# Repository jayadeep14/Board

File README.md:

# Custom Esp32 Board

This project is a custom-designed breakout board for the ESP32-S3 chip, created using KiCad 9. 
The board features native USB-C programming support, and includes an integrated Li-Ion battery charger, gyroscope 

# Hardware
Features
-ESP32-S3 Microcontroller

-USB-C Port

Used for both power input and firmware flashing

-Li-Ion Battery Charging Circuit

Integrated charger IC with status indicators

Supports single-cell Li-Ion/LiPo batteries
gyroscope 
-Compact Breakout Form Factor

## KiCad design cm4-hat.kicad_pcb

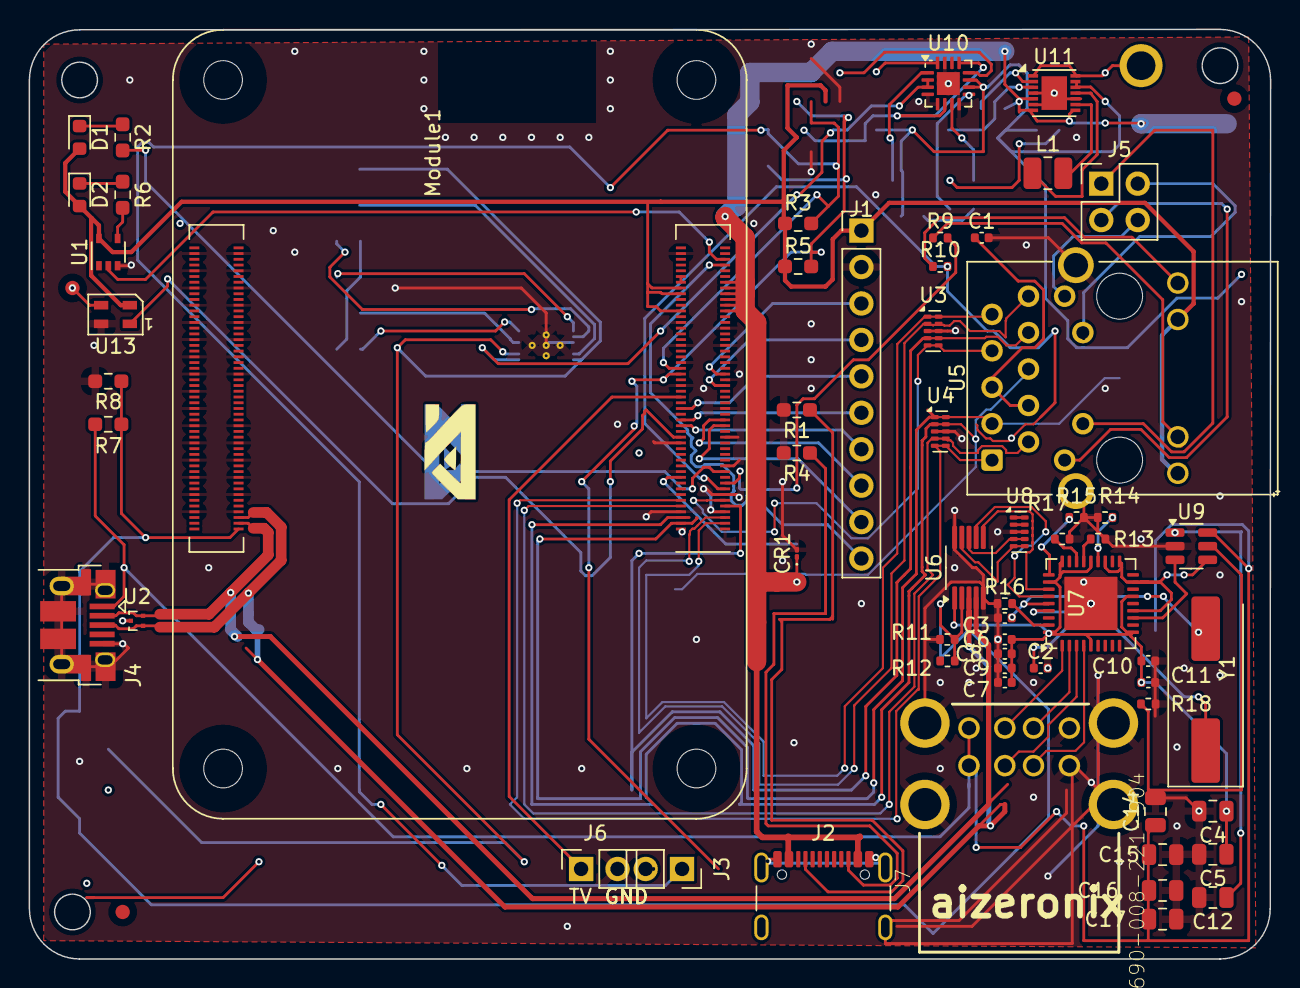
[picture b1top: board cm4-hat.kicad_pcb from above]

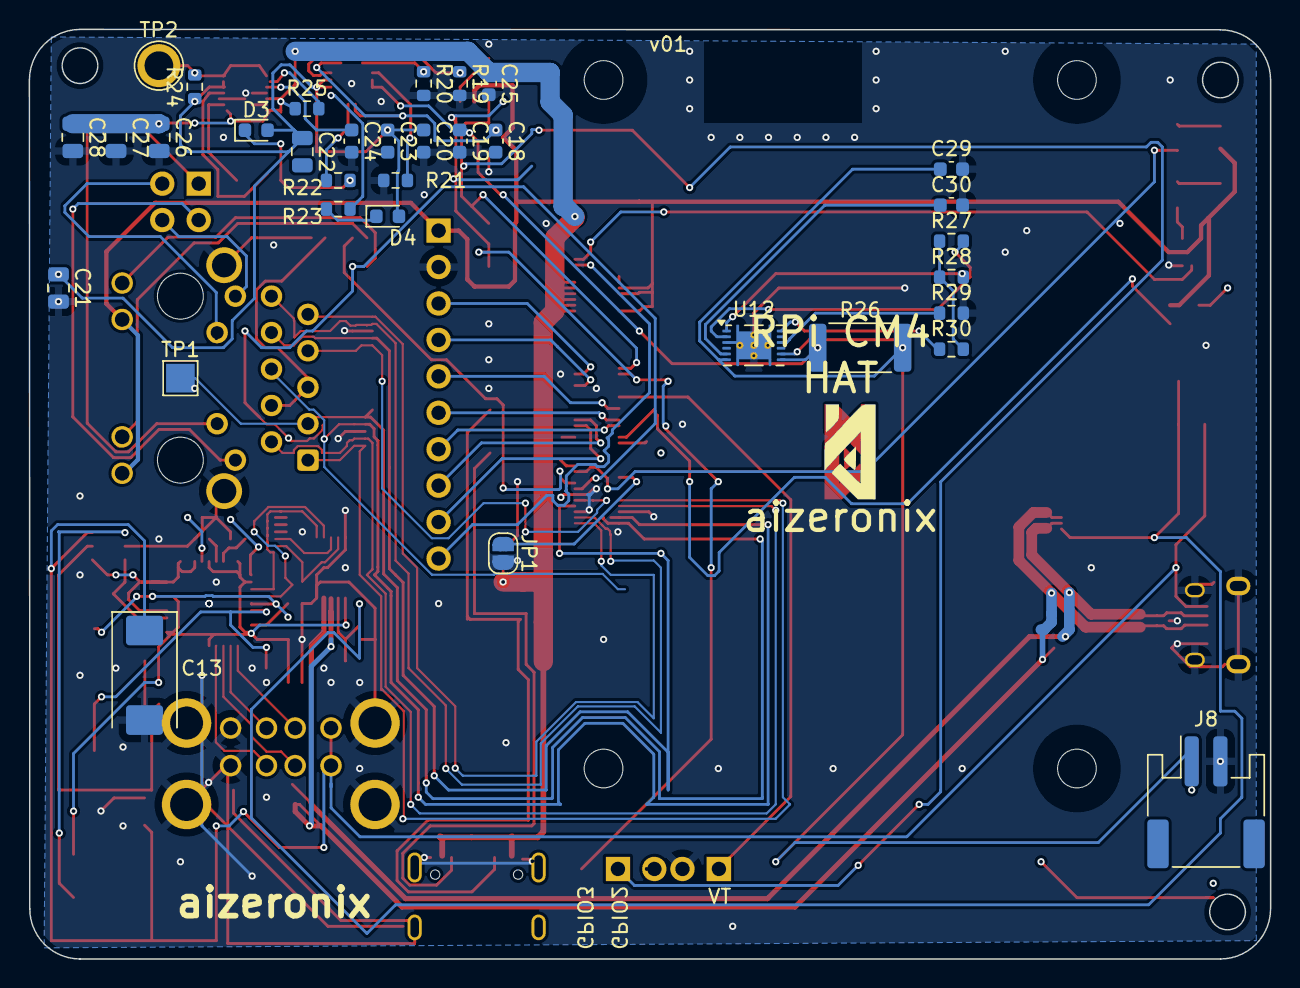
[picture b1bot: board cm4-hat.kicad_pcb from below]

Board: 2 copper layers, 86.5 x 64.8 mm, 94 parts (34 on the bottom side), 90 nets.

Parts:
C1, C6, C7, C8, C9, C10, C11: 100n; C_0402_1005Metric
C2, C3: 27pF; C_0402_1005Metric
C4, C5, C12, C14, C15, C16, C17: 10u; C_0805_2012Metric
C13: 100uF; CP_EIA-7343-31_Kemet-D
C18, C29: 1uF; C_0603_1608Metric
C19, C20: 4.7uF; C_0603_1608Metric
C21, C22: 10uF; C_0805_2012Metric
C23, C25: 10uF; C_0603_1608Metric
C24: 100nF; C_0603_1608Metric
C26, C27, C28: 22uF; C_0805_2012Metric
C30: 0.47uF; C_0603_1608Metric
CR1: SMBJ5.0A-TR; D_01005_0402Metric
D1: LED Green; LED_0603_1608Metric
D2: LED Red; LED_0603_1608Metric
D3: LED White; LED_0603_1608Metric
D4: LED Yellow; LED_0603_1608Metric
J1: DNP; PinHeader_1x10_P2.54mm_Vertical
J2: USB4105-GF-A; USB_C_Receptacle_GCT_USB4105-xx-A_16P_TopMnt_Horizontal
J3, J6: Conn_01x02_Pin; PinSocket_1x02_P2.54mm_Vertical
J4: USB_OTG; USB_Micro-B_EDAC_UCON00686
J5: THD-02-R; PinHeader_2x02_P2.54mm_Vertical
J7: 690-008-221-904; MOLEX_USB_67298-4090
J8: Battery In; JST_PH_S2B-PH-SM4-TB_1x02-1MP_P2.00mm_Horizontal
JP1: SolderJumper_2_Open; SolderJumper-2_P1.3mm_Open_RoundedPad1.0x1.5mm
L1: 1.5uH; L_1008_2520Metric
Module1: ComputeModule4-CM4; Raspberry-Pi-4-Compute-Module
R1, R4: 5.1k; R_0603_1608Metric_Pad0.98x0.95mm_HandSolder
R2, R6: 1k; R_0603_1608Metric_Pad0.98x0.95mm_HandSolder
R3, R5: DNP; R_0603_1608Metric_Pad0.98x0.95mm_HandSolder
R7, R8: 2.2K 1%; R_0603_1608Metric_Pad0.98x0.95mm_HandSolder
R9, R10: 470R; R_0402_1005Metric
R11, R12: 2.2K 1%; R_0402_1005Metric
R13, R14, R15, R17: 36K 1%; R_0402_1005Metric
R16: 12K 1%; R_0402_1005Metric
R18: 15K 1%; R_0402_1005Metric
R19: 3.3k; R_0603_1608Metric
R20: 1.8k; R_0603_1608Metric
R21, R24, R29, R30: 10k; R_0603_1608Metric
R22, R23: 1k; R_0603_1608Metric
R25: 100k; R_0603_1608Metric
R26: 0.010; R_2512_6332Metric
R27, R28: 5.1k; R_0603_1608Metric
TP1: TestPoint; TestPoint_Pad_2.0x2.0mm
TP2: TestPoint; TestPoint_Plated_Hole_D2.0mm
U1: 74LVC1G07SE-7; SOT-353_SC-70-5
U2: TPD2EUSB30; Texas_DRT-3
U3, U4, U8: TPD4EUSB30; USON-10_2.5x1.0mm_P0.5mm
U5: MagJack-A70-112-331N126; TRJG0926HENL
U6: FSUSB42MUX; MSOP-10_3x3mm_P0.5mm
U7: USB2514B-I/M2; QFN-36-1EP_6x6mm_P0.5mm_EP3.7x3.7mm
U9: AP22653W6; SOT-23-6
U10: BQ24075RGT; VQFN-16-1EP_3x3mm_P0.5mm_EP1.6x1.6mm
U11: TPS630701; DFN-14-1EP_3x3mm_P0.4mm_EP1.78x2.35mm
U12: BQ27441-G1; Texas_S-PDSO-N12
U13: 4492; LED_SK6805_PLCC4_2.4x2.7mm_P1.3mm
Y1: 24MHz; Crystal_SMD_HC49-SD
_: LOGO; aizeronix
_#2: LOGO; aizeronix

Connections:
+1.8V: Module1.88 (+1.8v_(Output)), Module1.90 (+1.8v_(Output))
+3.3V: D1.2 (A), D2.2 (A), J1.1, Module1.78 (GPIO_VREF(1.8v/3.3v_Input)), Module1.84 (+3.3v_(Output)), Module1.86 (+3.3v_(Output)), R3.1, R5.1, U1.5 (VCC), U5.15 (LEDG_A), U5.17 (LEDY_A), U13.2 (VDD)
+3V3: R27.1, R28.1, R30.2
+5V: C25.1, C26.1, C27.1, C28.1, CR1.1, Module1.77 (+5v_(Input)), Module1.79 (+5v_(Input)), Module1.81 (+5v_(Input)), Module1.83 (+5v_(Input)), Module1.85 (+5v_(Input)), Module1.87 (+5v_(Input)), R25.1, U11.5 (FB), U11.7 (VOUT), U11.8 (VOUT)
+BATT: C29.1, J8.1, R26.2, U12.6 (BAT), U12.8 (SRP)
/CM4 GPIO/EEPROM_nWP: JP1.1 (A), Module1.20 (EEPROM_nWP)
/CM4 GPIO/ETH_LEDG: Module1.17 (Ethernet_nLED2(3.3v)), R9.2
/CM4 GPIO/ETH_LEDY: Module1.15 (Ethernet_nLED3(3.3v)), R10.2
/CM4 GPIO/GPIO2: J3.1, Module1.58 (GPIO2), R3.2
/CM4 GPIO/GPIO3: J3.2, Module1.56 (GPIO3), R5.2
/CM4 GPIO/GPIO5: Module1.34 (GPIO5), U13.1 (DIN)
/CM4 GPIO/GPIO7: J1.9, Module1.37 (GPIO7)
/CM4 GPIO/GPIO8: J1.8, Module1.39 (GPIO8)
/CM4 GPIO/GPIO9: J1.6, Module1.40 (GPIO9)
/CM4 GPIO/GPIO10: J1.5, Module1.44 (GPIO10)
/CM4 GPIO/GPIO11: J1.7, Module1.38 (GPIO11)
/CM4 GPIO/GPIO14: J1.3, Module1.55 (GPIO14)
/CM4 GPIO/GPIO15: J1.4, Module1.51 (GPIO15)
/CM4 GPIO/GPIO27: J6.1, Module1.48 (GPIO27)
/CM4 GPIO/TR0_TAP: J5.3, U5.11 (VC1)
/CM4 GPIO/TR1_TAP: J5.1, U5.12 (VC2)
/CM4 GPIO/TR2_TAP: J5.2, U5.13 (VC3)
/CM4 GPIO/TR3_TAP: J5.4, U5.14 (VC4)
/CM4 GPIO/TRD0_N: Module1.10 (Ethernet_Pair0_N), U4.4 (D2+), U4.7, U5.2 (TRD0-)
/CM4 GPIO/TRD0_P: Module1.12 (Ethernet_Pair0_P), U4.5 (D2-), U4.6, U5.1 (TRD0+)
/CM4 GPIO/TRD1_N: Module1.6 (Ethernet_Pair1_N), U4.2 (D1-), U4.9, U5.6 (TRD1-)
/CM4 GPIO/TRD1_P: Module1.4 (Ethernet_Pair1_P), TP1.1, U4.1 (D1+), U4.10, U5.3 (TRD1+)
/CM4 GPIO/TRD2_N: Module1.9 (Ethernet_Pair2_N), U3.4 (D2+), U3.7, U5.8 (TRD2-)
/CM4 GPIO/TRD2_P: Module1.11 (Ethernet_Pair2_P), U3.5 (D2-), U3.6, U5.7 (TRD2+)
/CM4 GPIO/TRD3_N: Module1.5 (Ethernet_Pair3_N), U3.2 (D1-), U3.9, U5.10 (TRD3-)
/CM4 GPIO/TRD3_P: U3.1 (D1+), U3.10, U5.9 (TRD3+)
/CM4 GPIO/nLED_Activity: Module1.21 (PI_nLED_Activity), R2.2
/CM4 GPIO/nPWR_LED: Module1.95 (nPI_LED_PWR), U1.2
/CM4 GPIO/nRPIBOOT: J1.10, Module1.93 (nRPIBOOT)
/CM4 High Speed/BATT_OUT: C19.1, R26.1, U10.2 (BAT), U10.3 (BAT), U12.7 (SRN)
/CM4 High Speed/CHG_OUT: C20.1, C21.1, C22.1, C23.1, D3.2 (A), D4.2 (A), R24.1, U10.10 (OUT), U10.11 (OUT), U11.12 (VIN), U11.13 (VIN)
/CM4 High Speed/L1: L1.1, U11.11 (L1)
/CM4 High Speed/L2: L1.2, U11.9 (L2)
/CM4 High Speed/USB2-HUB/+3.3v: C4.1, C5.1, C6.1, C7.1, C8.1, C9.1, C10.1, C11.1, U6.1 (VCC), U7.5 (VDDA33), U7.10 (VDDA33), U7.15 (VDD33), U7.23 (VDD33), U7.27 (VBUS_DET), U7.29 (VDDA33), U7.36 (VDDA33)
/CM4 High Speed/USB2-HUB/+5v: C12.1, U9.1 (IN)
/CM4 High Speed/USB2-HUB/HD1_N: J7.2 (D-`), U7.1 (USBDM_DN1/PRT_DIS_M1)
/CM4 High Speed/USB2-HUB/HD1_P: J7.3 (D+`), U7.2 (USBDP_DN1/PRT_DIS_P1)
/CM4 High Speed/USB2-HUB/HD2_N: J7.6 (D-), U7.3 (USBDM_DN2/PRT_DIS_M2)
/CM4 High Speed/USB2-HUB/HD2_P: J7.7 (D+), U7.4 (USBDP_DN2/PRT_DIS_P2)
/CM4 High Speed/USB2-HUB/PWR1: U7.12 (PRTPWR1/BC_EN1), U9.3 (EN)
/CM4 High Speed/USB2-HUB/USBD_N: U6.8 (HSD1_M), U8.4 (D2+), U8.7
/CM4 High Speed/USB2-HUB/USBD_P: U6.9 (HSD1_P), U8.5 (D2-), U8.6
/CM4 High Speed/USB2-HUB/USBH_N: U6.6 (HSD0_M), U7.30 (USBDM_UP)
/CM4 High Speed/USB2-HUB/USBH_P: U6.7 (HSD0_P), U7.31 (USBDP_UP)
/CM4 High Speed/USB2-HUB/VBUS: C13.1, C14.1, C15.1, C16.1, C17.1, J7.1 (VBUS`), J7.5 (VBUS), U9.6 (OUT)
/CM4 High Speed/USB2-HUB/nOCS1: U7.13 (OCS_N1), U7.17 (OCS_N2), U7.19 (OCS_N3), U7.21 (OCS_N4), U9.4 (nFault)
/CM4 High Speed/USB2_N: J4.2 (D-), Module1.103 (USB2_N), U2.2 (D-), U6.4 (D_N)
/CM4 High Speed/USB2_P: J4.3 (D+), Module1.105 (USB2_P), U2.1 (D+), U6.3 (D_P)
/CM4 High Speed/USB_OTG_ID: Module1.101 (USB_OTG_ID), R7.2, R8.1, R11.1, R12.2, U6.2 (SEL)
/CM4 High Speed/~CHG: R23.2, U10.9 (~CHG)
/CM4 High Speed/~PGOOD: R22.2, U10.7 (~PGOOD)
GND: C1.2, C2.2, C3.2, C4.2, C5.2, C6.2, C7.2, C8.2, C9.2, C10.2, C11.2, C12.2, C13.2, C14.2, C15.2, C16.2, C17.2, C18.2, C19.2, C20.2, C21.2, C23.2, C24.2, C25.2, C26.2, C27.2, C28.2, C29.2, C30.2, CR1.2, J1.2, J4.5 (GND), J4.6 (Shield), J6.2, J7.4 (GND`), J7.8 (GND), J7.MT1, J7.MT2, J7.MT3, J7.MT4, J8.2, JP1.2 (B), Module1.1 (GND), Module1.2 (GND), Module1.7 (GND), Module1.8 (GND), Module1.13 (GND), Module1.14 (GND), Module1.22 (GND), Module1.23 (GND), Module1.32 (GND), Module1.33 (GND), Module1.42 (GND), Module1.43 (GND), Module1.52 (GND), Module1.53 (GND), Module1.59 (GND), Module1.60 (GND), Module1.65 (GND), Module1.66 (GND), Module1.71 (GND), Module1.74 (GND), Module1.98 (GND), Module1.107 (GND), Module1.108 (GND), Module1.113 (GND), Module1.114 (GND), Module1.119 (GND), Module1.120 (GND), Module1.125 (GND), Module1.126 (GND), Module1.131 (GND), Module1.132 (GND), Module1.137 (GND), Module1.138 (GND), Module1.144 (GND), Module1.150 (GND), Module1.155 (GND), Module1.156 (GND), Module1.161 (GND), Module1.162 (GND), Module1.167 (GND), Module1.168 (GND), Module1.173 (GND), Module1.174 (GND), Module1.179 (GND), Module1.180 (GND), Module1.185 (GND), Module1.186 (GND), Module1.191 (GND), Module1.192 (GND), Module1.197 (GND), Module1.198 (GND), R1.2, R4.2, R8.2, R11.2, R13.2, R14.2, R15.2, R16.1, R17.2, R18.2, R19.2, R20.2, R21.2, R29.2, U1.3 (GND), U2.3 (GND), U3.3 (GND), U3.8 (GND), U4.3 (GND), U4.8 (GND), U5.19 (SHIELD), U5.20 (SHIELD), U6.5 (GND), U6.10 (nOE), U7.37 (VSS), U8.3 (GND), U8.8 (GND), U9.2 (GND), U10.4 (~CE), U10.5 (EN2), U10.8 (VSS), U10.15 (SYSOFF), U10.17 (VSS), U11.4 (GND), U11.6 (FB2), U11.10 (PGND), U11.15 (VSEL), U12.3 (V_{SS}), U12.13 (PAD), U13.4 (GND)
unnamed: C1.1, U5.4 (CT), U5.5 (CT)
unnamed: D1.1 (K), R2.1
unnamed: D2.1 (K), R6.1
unnamed: D3.1 (K), R22.1
unnamed: D4.1 (K), R23.1
unnamed: J2.A5 (CC1), R1.1
unnamed: J2.B5 (CC2), R4.1
unnamed: J4.1 (VBUS), R7.1
unnamed: R6.2, U1.4
unnamed: R9.1, U5.16 (LEDG_K)
unnamed: R10.1, U5.18 (LEDY_K)
unnamed: R17.1, U7.25 (HS_IND/CFG_SEL1)
unnamed: R16.2, U7.35 (RBIAS)
unnamed: R13.1, U7.24 (SCL/SMBCLK/CFG_SEL0)
unnamed: R14.1, U7.22 (SDA/SMBDATA/NON_REM1)
unnamed: R15.1, U7.28 (SUSP_IND/LOCAL_PWR/NON_REM0)
unnamed: C2.1, U7.33 (XTALIN/CLKIN), Y1.1
unnamed: C3.1, U7.32 (XTALOUT), Y1.2
unnamed: U8.1 (D1+), U8.10
unnamed: U8.2 (D1-), U8.9
unnamed: R18.1, U9.5 (ILIM)
unnamed: R19.1, U10.12 (ILIM)
unnamed: R20.1, U10.16 (ISET)
unnamed: R21.1, U10.1 (TS)
unnamed: R24.2, TP2.1, U11.1 (PS/SYNC), U11.14 (EN)
unnamed: R25.2, U11.2 (PG)
unnamed: C24.1, U11.3 (VAUX)
unnamed: R29.1, U12.10 (BIN)
unnamed: R30.1, U12.12 (GPOUT)
unnamed: R27.2, U12.2 (SCL)
unnamed: R28.2, U12.1 (SDA)
unnamed: C30.1, U12.5 (V_{DD})
VBUS: C18.1, U10.6 (EN1), U10.13 (IN)

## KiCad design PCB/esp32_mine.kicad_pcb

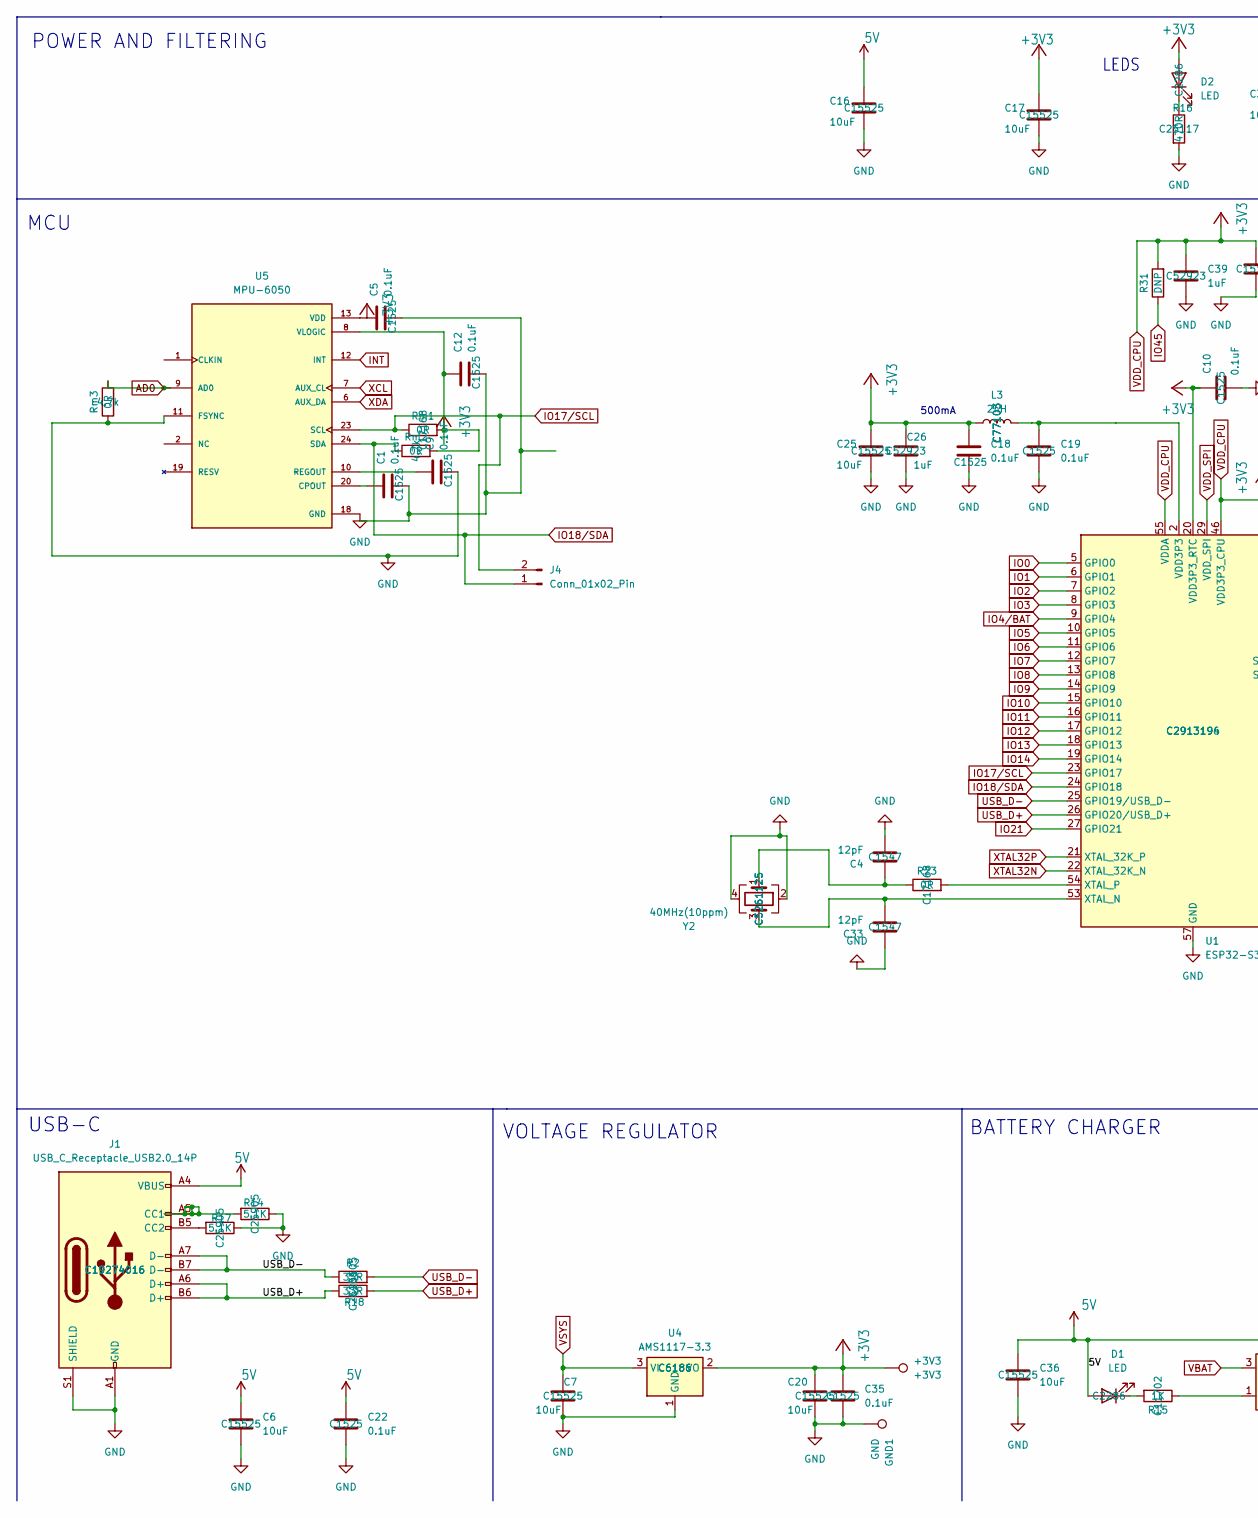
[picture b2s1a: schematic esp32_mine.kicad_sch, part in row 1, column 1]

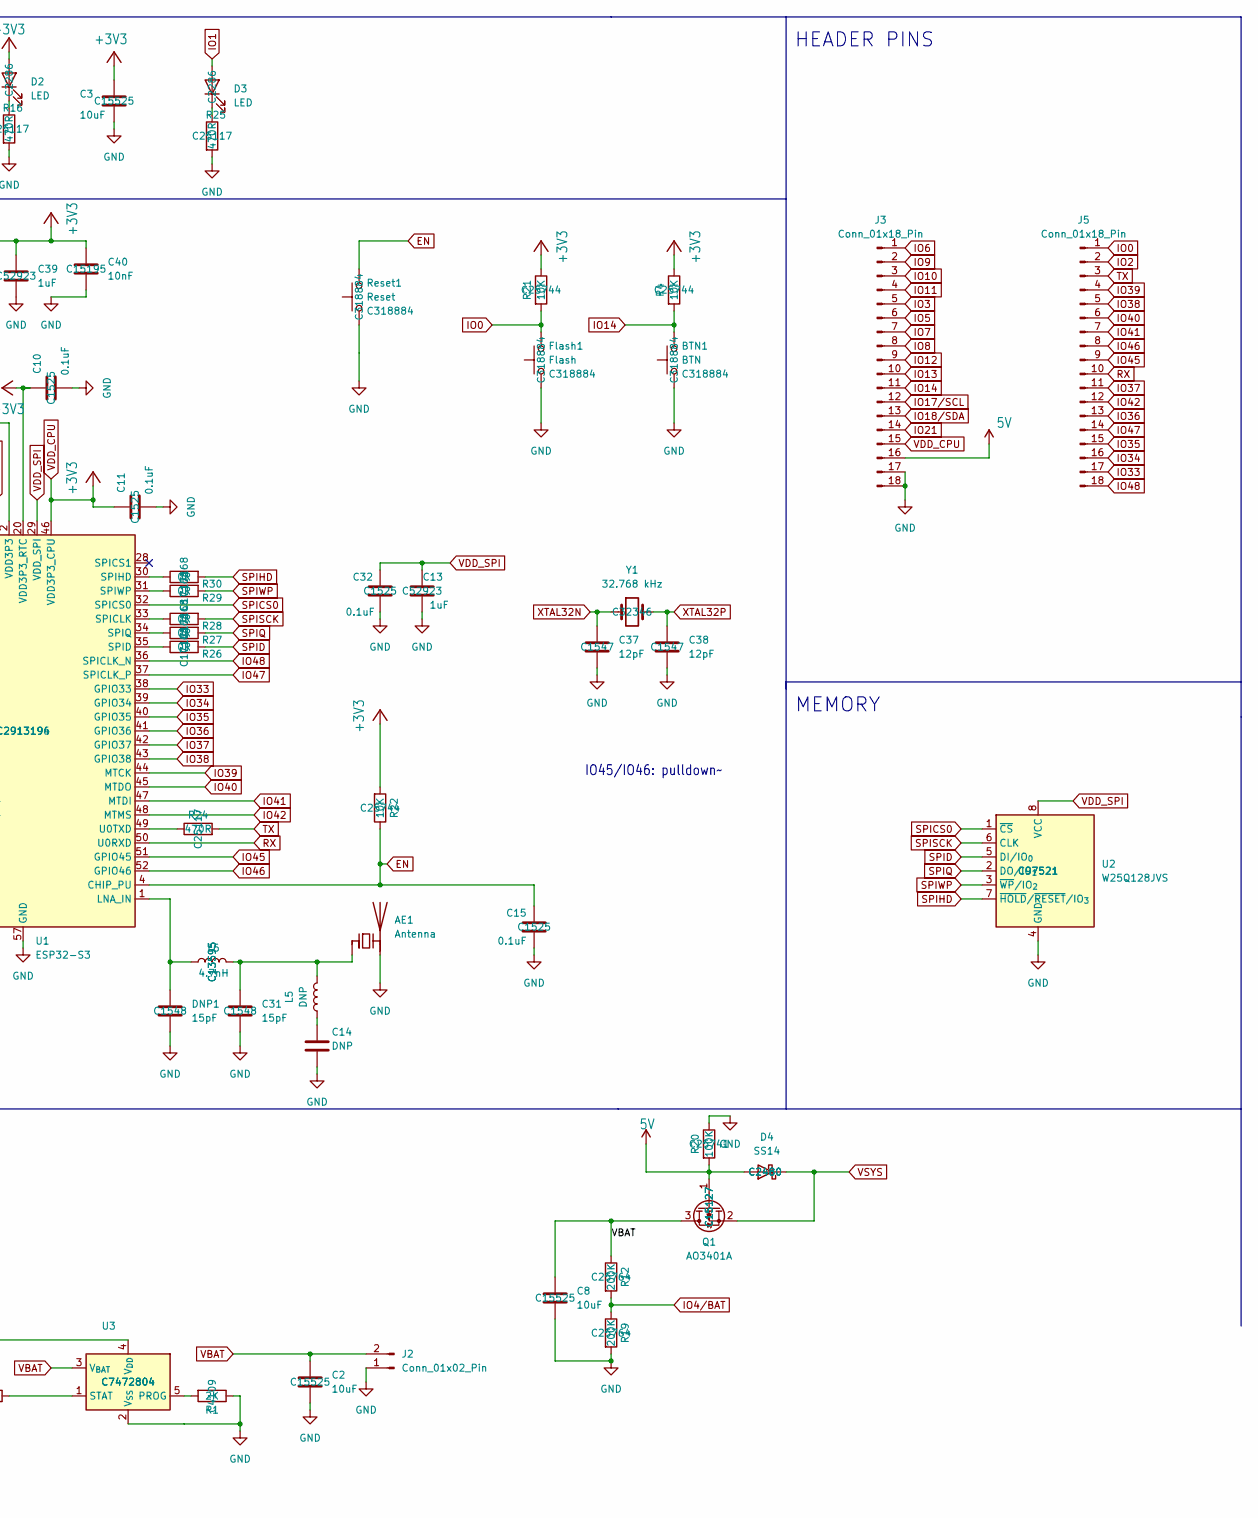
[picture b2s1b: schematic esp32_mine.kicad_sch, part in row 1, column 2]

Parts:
+3V3: +3V3; TestPoint_Pad_D1.0mm
AE1: Antenna; Texas_SWRA117D_2.4GHz_Left
BTN1: BTN; SW_Push_1P1T_XKB_TS-1187A; MNF PART NUMBER C318884; LCSC C318884
C1, C5, C9, C10, C11, C12, C15, C18, C19, C22, C32, C35: 0.1uF; C_0402_1005Metric; MNF PART NUMBER C1525; LCSC C1525
C2, C3, C6, C7, C8, C16, C17, C20, C25, C36: 10uF; C_0402_1005Metric; MNF PART NUMBER C15525; LCSC C15525
C4, C33, C37, C38: 12pF; C_0402_1005Metric; MNF PART NUMBER C1547; LCSC C1547
C13, C26, C39: 1uF; C_0402_1005Metric; MNF PART NUMBER C52923; LCSC C52923
C14: DNP; C_0402_1005Metric
C31: 15pF; C_0402_1005Metric; MNF PART NUMBER C1548; LCSC C1548
C40: 10nF; C_0402_1005Metric; MNF PART NUMBER C15195; LCSC C15195
D1, D2, D3: LED; LED_0603_1608Metric; MNF PART NUMBER C2286; LCSC C2286
D4: SS14; D_SMA; MNF PART NUMBER C2480; LCSC C2480
DNP1: 15pF; C_0402_1005Metric; MNF PART NUMBER C1548; LCSC C1548
Flash1: Flash; SW_Push_1P1T_XKB_TS-1187A; MNF PART NUMBER C318884; LCSC C318884
GND1: GND; TestPoint_Pad_D1.0mm
J1: USB_C_Receptacle_USB2.0_14P; USB_C_Receptacle_HCTL_HC-TYPE-C-16P-01A; MNF PART NUMBER C19274016; LCSC C19274016
J2, J4: Conn_01x02_Pin; PinSocket_1x02_P2.54mm_Vertical
J3, J5: Conn_01x18_Pin; PinHeader_1x18_P2.54mm_Vertical
L3: 2nH; L_0402_1005Metric; MNF PART NUMBER C77103; LCSC C77103
L5: DNP; L_0402_1005Metric
L6: 4.7nH; L_0402_1005Metric; MNF PART NUMBER C13595; LCSC C13595
Q1: AO3401A; SOT-23; MNF PART NUMBER C15127; LCSC C15127
R1: 2K; R_0402_1005Metric; MNF PART NUMBER C4109; LCSC C4109
R2, R18: 33R; R_0402_1005Metric; MNF PART NUMBER C25105; LCSC C25105
R4, R21, R22: 10K; R_0402_1005Metric; MNF PART NUMBER C25744; LCSC C25744
R12, R19: 200K; R_0402_1005Metric; MNF PART NUMBER C25764; LCSC C25764
R14, R17: 5.1K; R_0402_1005Metric; MNF PART NUMBER C25905; LCSC C25905
R15: 1K; R_0402_1005Metric; MNF PART NUMBER C11702; LCSC C11702
R16, R24, R25: 470R; R_0402_1005Metric; MNF PART NUMBER C25117; LCSC C25117
R20: 100K; R_0402_1005Metric; MNF PART NUMBER C25741; LCSC C25741
R23, R26, R27, R28, R29, R30: 0R; R_0402_1005Metric; MNF PART NUMBER C17168; LCSC C17168
R31: DNP; R_0402_1005Metric
Reset1: Reset; SW_Push_1P1T_XKB_TS-1187A; MNF PART NUMBER C318884; LCSC C318884
Rm1: 0R; R_0402_1005Metric; MNF PART NUMBER C17168; LCSC C17168
Rm2, Rm3: 0R; R_0402_1005Metric; MNF PART NUMBER C17168; LCSC 4.7k
U1: ESP32-S3; QFN-56-1EP_7x7mm_P0.4mm_EP4x4mm; MNF PART NUMBER C2913196; LCSC C2913194
U2: W25Q128JVS; SOIC-8_5.3x5.3mm_P1.27mm; MNF PART NUMBER C97521; LCSC C97521
U3: MCP73831-2-OT; SOT-23-5; MNF PART NUMBER C7472804; LCSC C7472804
U4: AMS1117-3.3; SOT-223-3_TabPin2; MNF PART NUMBER C6186; LCSC C6186
U5: MPU-6050; QFN50P400X400X95-24N; PARTREV 3.4
Y1: 32.768 kHz; Crystal_SMD_3215-2Pin_3.2x1.5mm; MNF PART NUMBER C32346; LCSC C32346
Y2: 40MHz(10ppm); Crystal_SMD_2520-4Pin_2.5x2.0mm; MNF PART NUMBER C5261125; LCSC C5261125

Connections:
5V: C6.1, C16.1, C22.1, C36.1, D1.2 (A), D4.2 (A), J1.A4 (VBUS), J1.A9 (VBUS), J1.B4 (VBUS), J1.B9 (VBUS), J3.16, Q1.1 (G), R20.2, U3.4 (V_{DD})
AD0: Rm3.2, U5.9 (AD0)
EN: C15.1, R22.1, Reset1.2, U1.4 (CHIP_PU)
GND: AE1.2 (PCB_Trace), BTN1.1, C2.2, C3.2, C4.2, C6.2, C7.2, C8.2, C9.2, C10.2, C11.2, C13.2, C14.2, C15.2, C16.2, C17.2, C18.2, C19.2, C20.2, C22.2, C25.2, C26.2, C31.2, C32.2, C33.1, C35.2, C36.2, C37.2, C38.2, C39.2, C40.2, DNP1.2, Flash1.1, GND1.1, J1.A1 (GND), J1.A12 (GND), J1.B1 (GND), J1.B12 (GND), J1.S1 (SHIELD), J2.1, J3.17, J3.18, R1.1, R14.1, R16.2, R17.1, R19.2, R20.1, R25.2, Reset1.1, Rm3.1, U1.57 (GND), U2.4 (GND), U3.2 (V_{SS}), U4.1 (GND), U5.11 (FSYNC), U5.18 (GND), Y2.2, Y2.4
INT: U5.12 (INT)
IO0: Flash1.2, J5.1, R21.2, U1.5 (GPIO0)
IO1: D3.2 (A), U1.6 (GPIO1)
IO2: J5.2, U1.7 (GPIO2)
IO3: J3.5, U1.8 (GPIO3)
IO4/BAT: R12.2, R19.1, U1.9 (GPIO4)
IO5: J3.6, U1.10 (GPIO5)
IO6: J3.1, U1.11 (GPIO6)
IO7: J3.7, U1.12 (GPIO7)
IO8: J3.8, U1.13 (GPIO8)
IO9: J3.2, U1.14 (GPIO9)
IO10: J3.3, U1.15 (GPIO10)
IO11: J3.4, U1.16 (GPIO11)
IO12: J3.9, U1.17 (GPIO12)
IO13: J3.10, U1.18 (GPIO13)
IO14: BTN1.2, J3.11, R4.2, U1.19 (GPIO14)
IO17/SCL: J3.12, J4.2, Rm1.1, U1.23 (GPIO17), U5.23 (SCL)
IO18/SDA: J3.13, J4.1, Rm2.1, U1.24 (GPIO18), U5.24 (SDA)
IO21: J3.14, U1.27 (GPIO21)
IO33: J5.17, U1.38 (GPIO33)
IO34: J5.16, U1.39 (GPIO34)
IO35: J5.15, U1.40 (GPIO35)
IO36: J5.13, U1.41 (GPIO36)
IO37: J5.11, U1.42 (GPIO37)
IO38: J5.5, U1.43 (GPIO38)
IO39: J5.4, U1.44 (MTCK)
IO40: J5.6, U1.45 (MTDO)
IO41: J5.7, U1.47 (MTDI)
IO42: J5.12, U1.48 (MTMS)
IO45: J5.9, R31.1, U1.51 (GPIO45)
IO46: J5.8, U1.52 (GPIO46)
IO47: J5.14, U1.37 (SPICLK_P)
IO48: J5.18, U1.36 (SPICLK_N)
unnamed: AE1.1 (FEED), C31.1, L5.2, L6.2
unnamed: C1.2, C5.2, C12.2
unnamed: C4.1, R23.1, Y2.1
unnamed: C14.1, L5.1
unnamed: C19.1, L3.2, U1.2 (VDD3P3), U1.3 (VDD3P3)
unnamed: D1.1 (K), R15.2
unnamed: D2.1 (K), R16.1
unnamed: D3.1 (K), R25.1
unnamed: J1.A5 (CC1), R14.2
unnamed: J1.B5 (CC2), R17.2
unnamed: DNP1.1, L6.1, U1.1 (LNA_IN)
unnamed: R28.1, U1.33 (SPICLK)
unnamed: R26.1, U1.35 (SPID)
unnamed: R30.1, U1.30 (SPIHD)
unnamed: R27.1, U1.34 (SPIQ)
unnamed: R29.1, U1.31 (SPIWP)
unnamed: R24.1, U1.49 (U0TXD)
unnamed: C33.2, U1.53 (XTAL_N), Y2.3
unnamed: R23.2, U1.54 (XTAL_P)
unnamed: R1.2, U3.5 (PROG)
unnamed: R15.1, U3.1 (STAT)
unnamed: C1.1, U5.20 (CPOUT)
unnamed: U5.2 (NC), U5.3 (NC), U5.4 (NC), U5.5 (NC), U5.14 (NC), U5.15 (NC), U5.16 (NC), U5.17 (NC)
unnamed: C9.1, U5.10 (REGOUT)
unnamed: C5.1, U5.13 (VDD)
RX: J5.10, U1.50 (U0RXD)
SPICS0: U1.32 (SPICS0), U2.1 (~CS)
SPID: R26.2, U2.5 (DI/IO_{0})
SPIHD: R30.2, U2.7 (~HOLD/~RESET/IO_{3})
SPIQ: R27.2, U2.2 (DO/IO_{1})
SPISCK: R28.2, U2.6 (CLK)
SPIWP: R29.2, U2.3 (~WP/IO_{2})
TX: J5.3, R24.2
USB_D+: J1.A6 (D+), J1.B6 (D+), R18.1, R18.2, U1.26 (GPIO20/USB_D+)
USB_D-: J1.A7 (D-), J1.B7 (D-), R2.1, R2.2, U1.25 (GPIO19/USB_D-)
VBAT: C2.1, C8.1, J2.2, Q1.3 (D), R12.1, U3.3 (V_{BAT})
VDD_CPU: +3V3.1, C3.1, C10.1, C11.1, C12.1, C17.1, C18.1, C20.1, C25.1, C26.1, C35.1, C39.1, C40.1, D2.2 (A), J3.15, L3.1, R4.1, R21.1, R22.2, R31.2, Rm1.2, Rm2.2, U1.20 (VDD3P3_RTC), U1.46 (VDD3P3_CPU), U1.55 (VDDA), U1.56 (VDDA), U4.2 (VO), U5.8 (VLOGIC)
VDD_SPI: C13.1, C32.1, U1.29 (VDD_SPI), U2.8 (VCC)
VSYS: C7.1, D4.1 (K), Q1.2 (S), U4.3 (VI)
XCL: U5.7 (AUX_CL)
XDA: U5.6 (AUX_DA)
XTAL32N: C37.1, U1.22 (XTAL_32K_N), Y1.1
XTAL32P: C38.1, U1.21 (XTAL_32K_P), Y1.2

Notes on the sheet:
BATTERY CHARGER
VOLTAGE REGULATOR
500mA
LEDS
MCU
HEADER PINS
MEMORY
POWER AND FILTERING
IO45/IO46: pulldown~~{}
USB-C

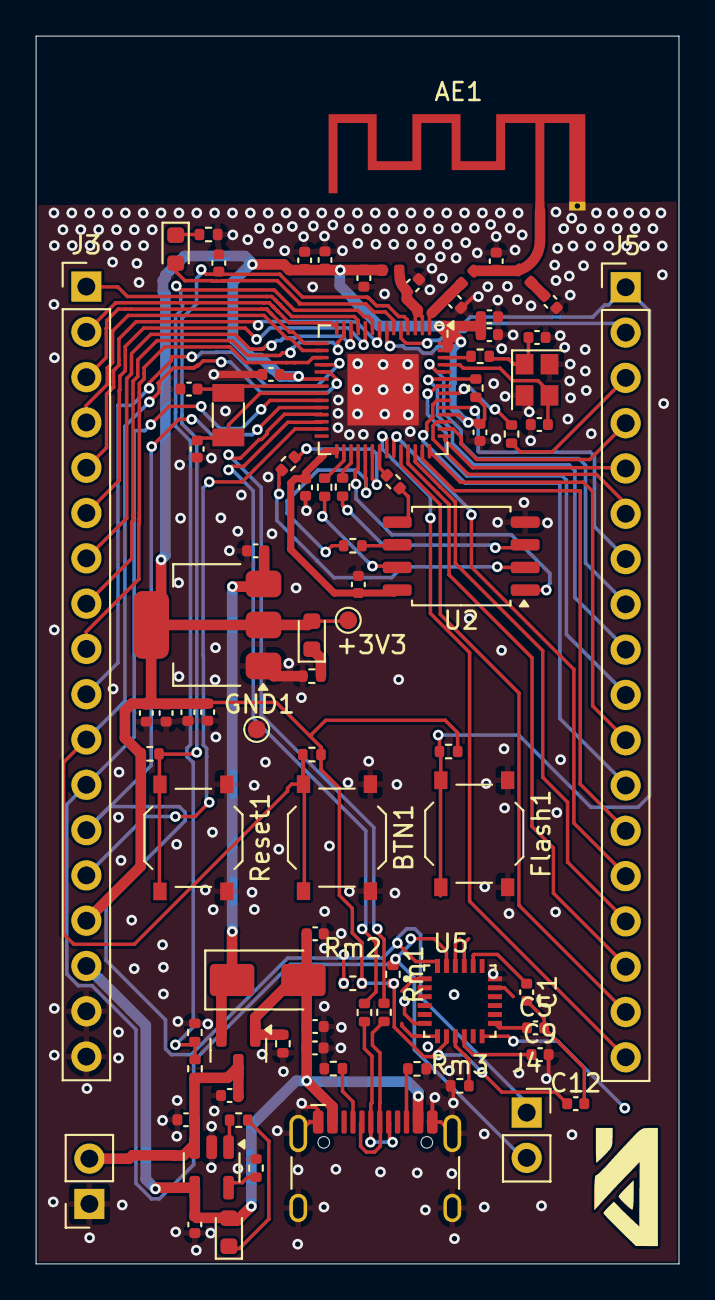
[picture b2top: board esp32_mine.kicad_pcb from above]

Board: 2 copper layers, 36.0 x 68.8 mm, 85 parts (0 on the bottom side), 77 nets.

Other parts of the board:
_: LOGO; aizeronix

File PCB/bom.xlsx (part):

JLCPCB BOM Tool - BOM Matching
BOM name：bom-JLCPCB Assembly Order.xlsx |  |  | Download Time：2025-11-22 14:38:48 |  |  |  | * Our matching results are updated in real-time, but stock and prices may chang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
PCB Assembled Qty：5 |  |  | Est. Total Price：12.1464
Your BOM |  |  |  |  | Matched Parts |  |  |  |  |  |  | Order Information
Top Designator | Bottom Designator | Comment | Footprint | JLCPCB Part # | Matches | Part # | Manufacturer | Footprint | Description | Category | Warning | JLCPCB Part # | Product link | Lib Type | Qty | Source | Total Price ($)
BTN1 |  | BTN | SW_Push_1P1T_XKB_TS-1187A |  | Select by Customer | TS-1187A-B-A-B | XKB Connection | SMD-4P,5.1x5.1mm | -30℃~+85℃ 1.5mm 1.6N 100,000 Cycles 12V 5.1mm 5.1mm 50mA Gold No Round Button S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 | Tactile Switches | 1.Multiple lines in the BOM have been matched to the same part. Please check if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 | C318884 | https://jlcpcb.com/partdetail/XKBConnection-TS_1187A_B_AB/C318884 | Basic | 6.0 | 6 JLCPCB | 0.1116
FLASH1 |  | Flash | SW_Push_1P1T_XKB_TS-1187A |  | Select by Customer
RESET1 |  | Reset | SW_Push_1P1T_XKB_TS-1187A |  | Select by Customer
C10,C11,C15,C18,C19,C22,C32,C35 |  | 0.1uF | 0402 |  | Unconfirmed | CL05B104KO5NNNC | Samsung Electro-Mechanics | 0402 | 100nF 16V X7R ±10% 0402 Multilayer Ceramic Capacitors MLCC - SMD/SMT ROHS | Multilayer Ceramic Capacitors MLCC - SMD/SMT | 1.The comment (CL05B104KO5NNNC) of this part does not match the one (0.1uF) pro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 | C1525 | https://jlcpcb.com/partdetail/1877-CL05B104KO5NNNC/C1525 | Basic | 16.0 | 16 JLCPCB | 0.0192
C13,C26,C39 |  | 1uF | 0402 |  | Select by System | CL05A105KA5NQNC | Samsung Electro-Mechanics | 0402 | 1uF 25V X5R ±10% 0402 Multilayer Ceramic Capacitors MLCC - SMD/SMT ROHS | Multilayer Ceramic Capacitors MLCC - SMD/SMT |  | C52923 | https://jlcpcb.com/partdetail/53938-CL05A105KA5NQNC/C52923 | Basic | 6.0 | 6 JLCPCB | 0.0174
C16,C17,C2,C20,C25,C3,C36,C6,C7,C8 |  | 10uF | 0402 |  | Select by System | CL05A106MQ5NUNC | Samsung Electro-Mechanics | 0402 | 10uF 6.3V X5R ±20% 0402 Multilayer Ceramic Capacitors MLCC - SMD/SMT ROHS | Multilayer Ceramic Capacitors MLCC - SMD/SMT |  | C15525 | https://jlcpcb.com/partdetail/16204-CL05A106MQ5NUNC/C15525 | Basic | 20.0 | 20 JLCPCB | 0.09
C31,DNP1 |  | 15pF | 0402 |  | Unconfirmed | 0402CG150J500NT | FH (Guangdong Fenghua Advanced Tech) | 0402 | 15pF 50V C0G ±5% 0402 Multilayer Ceramic Capacitors MLCC - SMD/SMT ROHS | Multilayer Ceramic Capacitors MLCC - SMD/SMT | 1.There may be multiple types of parts, but one type of part has been matched. 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 | C1548 | https://jlcpcb.com/partdetail/1900-0402CG150J500NT/C1548 | Basic | 4.0 | 4 JLCPCB | 0.004
C33,C37,C38,C4 |  | 12pF | 0402 |  | Select by System | 0402CG120J500NT | FH (Guangdong Fenghua Advanced Tech) | 0402 | 12pF 50V C0G ±5% 0402 Multilayer Ceramic Capacitors MLCC - SMD/SMT ROHS | Multilayer Ceramic Capacitors MLCC - SMD/SMT |  | C1547 | https://jlcpcb.com/partdetail/1899-0402CG120J500NT/C1547 | Basic | 8.0 | 8 JLCPCB | 0.0088
C40 |  | 10nF | 0402 |  | Select by System | CL05B103KB5NNNC | Samsung Electro-Mechanics | 0402 | 10nF 50V X7R ±10% 0402 Multilayer Ceramic Capacitors MLCC - SMD/SMT ROHS | Multilayer Ceramic Capacitors MLCC - SMD/SMT |  | C15195 | https://jlcpcb.com/partdetail/15869-CL05B103KB5NNNC/C15195 | Basic | 2.0 | 2 JLCPCB | 0.0028
D1,D2,D3 |  | LED | 0603 |  | Unconfirmed | KT-0603R | Hubei KENTO Elec | 0603 | -40℃~+85℃ 120° 2.4V 20mA 300mcd 40mW 615nm~630nm 645nm Red Water Clear 0603 LED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 | LED Indication - Discrete | 1.The comment (KT-0603R) of this part does not match the one (LED) provided in 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 | C2286 | https://jlcpcb.com/partdetail/Hubei_KENTOElec-KT0603R/C2286 | Basic | 6.0 | 6 JLCPCB | 0.0336
D4 |  | SS14 | D_SMA |  | Select by System | SS14 | MDD(Microdiode Semiconductor) | SMA(DO-214AC) | -55℃~+150℃ 1A 25A 300uA@40V 40V 550mV@1A Independent SMA(DO-214AC) Schottky Dio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 | Schottky Diodes |  | C2480 | https://jlcpcb.com/partdetail/MDD_Microdiode_Semiconductor-S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 | Basic | 2.0 | 2 JLCPCB | 0.0298
J1 |  | USB_C_Receptacle_USB2.0_14P | USB_C_Receptacle_HCTL_HC-TYPE-C-16P-01A |  | Select by Customer | HC-TYPE-C-16P-01A | HCTL | SMD | -55℃~+85℃ 1 16P 5A Female Surface Mount, Right Angle Type-C SMD USB Connectors 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 | USB Connectors |  | C2894897 | https://jlcpcb.com/partdetail/HCTL-HC_TYPE_C_16P01A/C2894897 | Extended | 2.0 | 2 JLCPCB | 0.1746
J2,J4 |  | Conn_01x02_Pin | PinSocket_1x02_P2.54mm_Vertical |  | Select by Customer | HX PZ2.54-1x2P TP-YQ | hanxia | SMD,P=2.54mm(交错脚) | -40℃~+105℃ 1 1kV 1x2P 2.54mm 2.5mm 2P 3A 6mm Black Brass Gold Pin Header Surfac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 | Pin Headers |  | C41417359 | https://jlcpcb.com/partdetail/hanxia-HX_PZ2_54_1x2P_TPYQ/C41417359 | Extended | 5.0 | 5 JLCPCB | 0.1125
J3,J5 |  | Conn_01x18_Pin | PinHeader_1x18_P2.54mm_Vertical |  | Select by Customer | DS1021-1x18SF11-B | CONNFLY Elec | 插件,P=2.54mm | -40℃~+105℃ 1 18P 1x18P 2.54mm 250V 3A Black Copper Alloy Gold Pin Header Throug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 | Pin Headers |  | C7430374 | https://jlcpcb.com/partdetail/CONNFLYElec-DS1021_1x18SF11B/C7430374 | Extended | 4.0 | 4 JLCPCB | 0.296
L3 |  | 2nH | 0402 |  | Select by System | LQG15HS2N0S02D | Murata Electronics | 0402 | 2nH 6GHz 8@100MHz 900mA 90mΩ 0402 Inductors (SMD) ROHS | Inductors (SMD) |  | C18216 | https://jlcpcb.com/partdetail/MurataElectronics-LQG15HS2N0S0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 | Extended | 20.0 | 20 JLCPCB | 0.15
L6 |  | 4.7nH | 0402 |  | Select by System | LQG15HS4N7S02D | Murata Electronics | 0402 | 160mΩ 4.7nH 6GHz 700mA 8@100MHz 0402 Inductors (SMD) ROHS | Inductors (SMD) |  | C86065 | https://jlcpcb.com/partdetail/MurataElectronics-LQG15HS4N7S0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 | Extended | 20.0 | 20 JLCPCB | 0.15
Q1 |  | AO3401A | SOT-23 |  | Select by System | AO3401A | Alpha & Omega Semicon | SOT-23 | 1 P-Channel 14nC@10V 30V 47mΩ@10V 4A 55pF 645pF 80pF 900mV@250uA SOT-23 MOSFETs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 | MOSFETs |  | C15127 | https://jlcpcb.com/partdetail/Alpha_OmegaSemicon-AO3401A/C15127 | Basic | 2.0 | 2 JLCPCB | 0.111
R1 |  | 2K | 0402 |  | Unconfirmed | 0402WGF2001TCE | UNI-ROYAL(Uniroyal Elec) | 0402 | -55℃~+155℃ 2kΩ 50V 62.5mW Thick Film Resistor ±1% ±100ppm/℃ 0402 Chip Resistor 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 | Chip Resistor - Surface Mount | 1.The comment (0402WGF2001TCE) of this part does not match the one (2K) provide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 | C4109 | https://jlcpcb.com/partdetail/4516-0402WGF2001TCE/C4109 | Basic | 2.0 | 2 JLCPCB | 0.0012
R12,R19 |  | 200K | 0402 |  | Unconfirmed | 0402WGF2003TCE | UNI-ROYAL(Uniroyal Elec) | 0402 | -55℃~+155℃ 200kΩ 50V 62.5mW Thick Film Resistor ±1% ±100ppm/℃ 0402 Chip Resisto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 | Chip Resistor - Surface Mount | 1.The comment (0402WGF2003TCE) of this part does not match the one (200K) provi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 | C25764 | https://jlcpcb.com/partdetail/26507-0402WGF2003TCE/C25764 | Basic | 4.0 | 4 JLCPCB | 0.0024
R14,R17 |  | 5.1K | 0402 |  | Unconfirmed | 0402WGF5101TCE | UNI-ROYAL(Uniroyal Elec) | 0402 | -55℃~+155℃ 5.1kΩ 50V 62.5mW Thick Film Resistor ±1% ±100ppm/℃ 0402 Chip Resisto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 | Chip Resistor - Surface Mount | 1.The comment (0402WGF5101TCE) of this part does not match the one (5.1K) provi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 | C25905 | https://jlcpcb.com/partdetail/26648-0402WGF5101TCE/C25905 | Basic | 4.0 | 4 JLCPCB | 0.002
R15 |  | 1K | 0402 |  | Unconfirmed | 0402WGF1001TCE | UNI-ROYAL(Uniroyal Elec) | 0402 | -55℃~+155℃ 1kΩ 50V 62.5mW Thick Film Resistor ±1% ±100ppm/℃ 0402 Chip Resistor 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 | Chip Resistor - Surface Mount | 1.The comment (0402WGF1001TCE) of this part does not match the one (1K) provide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 | C11702 | https://jlcpcb.com/partdetail/12256-0402WGF1001TCE/C11702 | Basic | 2.0 | 2 JLCPCB | 0.0012
R16,R24,R25 |  | 470R | 0402 |  | Unconfirmed | 0402WGF4700TCE | UNI-ROYAL(Uniroyal Elec) | 0402 | -55℃~+155℃ 470Ω 50V 62.5mW Thick Film Resistor ±1% ±100ppm/℃ 0402 Chip Resistor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 | Chip Resistor - Surface Mount | 1.The comment (0402WGF4700TCE) of this part does not match the one (470R) provi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 | C25117 | https://jlcpcb.com/partdetail/25860-0402WGF4700TCE/C25117 | Basic | 6.0 | 6 JLCPCB | 0.0036
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
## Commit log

2025-11-17 Add README for custom ESP32 board project
    Added project overview and hardware features for the custom ESP32 board.
2025-11-17 Add initial content to Text.txt
2025-11-17 Rename PCB/esp32_mine.zip to Gerber.zip
2025-11-17 Rename Gerber.zip to PCB/Gerber.zip
2025-11-18 Expand README with project details and features
    Added project overview, key features, hardware design, PCB design, challenges, and next steps for the ESP32-S3 breakout board.
2025-11-19 Refactor README for clarity and conciseness
    Removed redundant project details and streamlined the README content for clarity.
2025-11-21 Rename base_.step to base.step
2025-11-22 Rename esp32_mine.pdf to esp32_mine_layer.pdf
2025-11-22 Restore positions.csv with original content
2025-11-22 Rename esp32_mine-.zip to Gerber_.zip
2025-11-22 Rename esp32_mine.pdf to Schematic.pdf
2025-11-29 Rename gerbers.zip to Production/gerbers.zip
2025-11-29 Rename cm4-hat.pdf to layers.pdf
2025-11-29 Rename cm4-hat-all-pos.csv to BOM.csv
